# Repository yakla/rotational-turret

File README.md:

# infinit Rotational Smart Tracking Camera

first i started the project as a idea for a consept for a rotating turret that can go forever without needing to retract. i wanted to make it a concept so i made the build realy small but after i designed the base and then decited to go all out and make a follower cammera. in the end it ended up super small in just 10cm×10cm×9cm. for me its just a fun project to do in the meantime of the war currently. 

## Mechanics & Power
The project uses a high speed brushless motor to rotate the base gear and a very small servo to rotate the head.
The power uses usb c 12v and buck convertor to power everything and passes the data and the power throught a slip ring  inside the shaft .

## Communication & Vision Pipeline
To comunicate with other devices and transfer the stream it uses a udp server to get the ip of the device and send back the camera data to it for high speed transfer and low cpu usage on the small esp . 
It also uses bluetooth for manual movment mode. 
For the color pipeline i use a optimised version of rgb to hsv and color range checking for each pixel summing the position and getting the aproximet position to rotate to.

## Modes
the turret has 3 main modes.
* Manual that streams with jpeg optimised stream and let the user control the turret
* Follower that sets the turret to follow the target (for now set in the code)
* Lock that send the data of the target position without following it

## Design & Hardware
For the head i designed a costume pcb to fit the tof sensor the esp camera and the leds.
For a encloseure i use a thin sheet of invisable plastic that rotates with the turret. that make it realy cool in my opinion.

CAD Link : https://cad.onshape.com/documents/5493d3bfb7c584824d124c44/w/b9fe300d7cd71857bff2772f/e/d3c804d532ca15a2a7af37b9?renderMode=0&uiState=69b6b6c78c596208d828381b

For the Hardware i used:
* XIAO ESP32-S3 - Main Controller & Vision Processing
* PTK 7308H Servo - Pan/Tilt Movement
* Emax ECO 1407 Motor - Turret Movement
* Custom PCB - Power distribution, Leds & sensor integration
*  - Distance detection (ToF)
   - Camera OV2640
   - SK6805 NeoPixel

## Project Status & Roadmap
- [ ] Mobile App for Remote control and setting Wifi detection and simple viewing window (Planned)
- [x] Design the project with a cheaper servo (Planned) 

## How to use
* **Build:** Use PlatformIO to flash the Firmware/ folder to the XIAO.
* **Setup_bluetooth:** Connect to the device via Bluetooth.
* **Setup_wifi:** Currently have to set it in the main code. will probebly add a way in the app later
* **UDP_client** you can use the python code in tools folder of the firmware currently. Will add a viewing window in the app later
* **Run:** Point the camera at a target object; the turret will lock on using the HSV threshold defined in config.h.

## Credits
* Designed and built as part of Hack Club.

## BOM
| Item                               | Description                                                   | Quantity             | Unit Price ($) | Total Price ($) | URL |
|:-----------------------------------|:--------------------------------------------------------------|:---------------------|:---------------|:----------------|:----|
| Hobbywing Skywalker 12A            | esc for the brushless motor                                   | 1                    | $5.23          | $5.23           | https://he.aliexpress.com/item/1005006848267224.html |
| Emax ECO 1407 Motor 2800KV         | the brushless motor for the base turret rotation              | 1                    | $12.39         | $16.11          | https://he.aliexpress.com/item/1005006857011061.html |
| Ptk 7308h                          | the servo that moves the head of the camera                   | 1                    | $27.00         | $27.16          | https://he.aliexpress.com/item/1005005891940798.html |
| slip ring 6.5mm 8ch a1             | the most important part to move electucity even when rotating | 1                    | $4.04          | $7.04           | https://he.aliexpress.com/item/1005009463382321.html |
| USB-C PD PD/QC Decoy Board         | the usb port                                                  | 1                    | $1.30          | $1.30           | https://he.aliexpress.com/item/1005005622939899.html |
| Mini360 buck convertor             | get the usb voltage down                                      | 1                    | $0.28          | $1.74           |https://he.aliexpress.com/item/1005008724925620.html |
| XIAO ESP32-S3 Sense                | the brain                                                     | 1                    | $13.85         | $17.21          | https://he.aliexpress.com/item/1005005544155799.html |
| Adafruit VL53L4CX                  | the tof sensor                                                | 1                    | $19.57         | $19.57          | https://he.aliexpress.com/item/1005010327402661.html |
| SK6805 2427                        | neopixel for the pcb                                          | 1 (50 in one order)  | $3.73          | $6.30           | https://he.aliexpress.com/item/1005008979678361.html|
| capcacitor 100nf 0805              | just there for the neopixel                                   | 1 (100 in one order) | $1.24          | $1.24           | https://he.aliexpress.com/item/1005005293453925.html |
| capcacitor 10uf 1206               | just there for the neopixel                                   | 1 (20 in one order)  | $1.35          | $1.35           | https://he.aliexpress.com/item/1005007363840397.html |
| resestor 47R 0805                  | for the neopixel din                                          | 1 (100 in one order) | $1.11          | $1.11           | https://he.aliexpress.com/item/32382494431.html |
|o-ring thickring 2mm 26mm od        |for the conveyor of the head spin                              |1(100 in one order)   |1.99$           |$1.99            |https://he.aliexpress.com/item/1005006851111300.html |
|PCB                              	 |the PCB	             |1 (5 for one order)	                 |$2.00	                |$7.29|https://www.elecrow.com
|6000-2RS Bearing 10mm id 26mm od|for low friction shaft rotation|1 (4 for one order)|$3.12|$3.12|https://he.aliexpress.com/item/1005006079201259.html|
|Clamp shaft lock Ring Collar 10mm|to hold the shaft better|1|$2.73|$2.73|https://he.aliexpress.com/item/1005006211797860.html|
**Sum** |                                                               |                      | **$100.93** | **$120.49** current price **$105.10** | |

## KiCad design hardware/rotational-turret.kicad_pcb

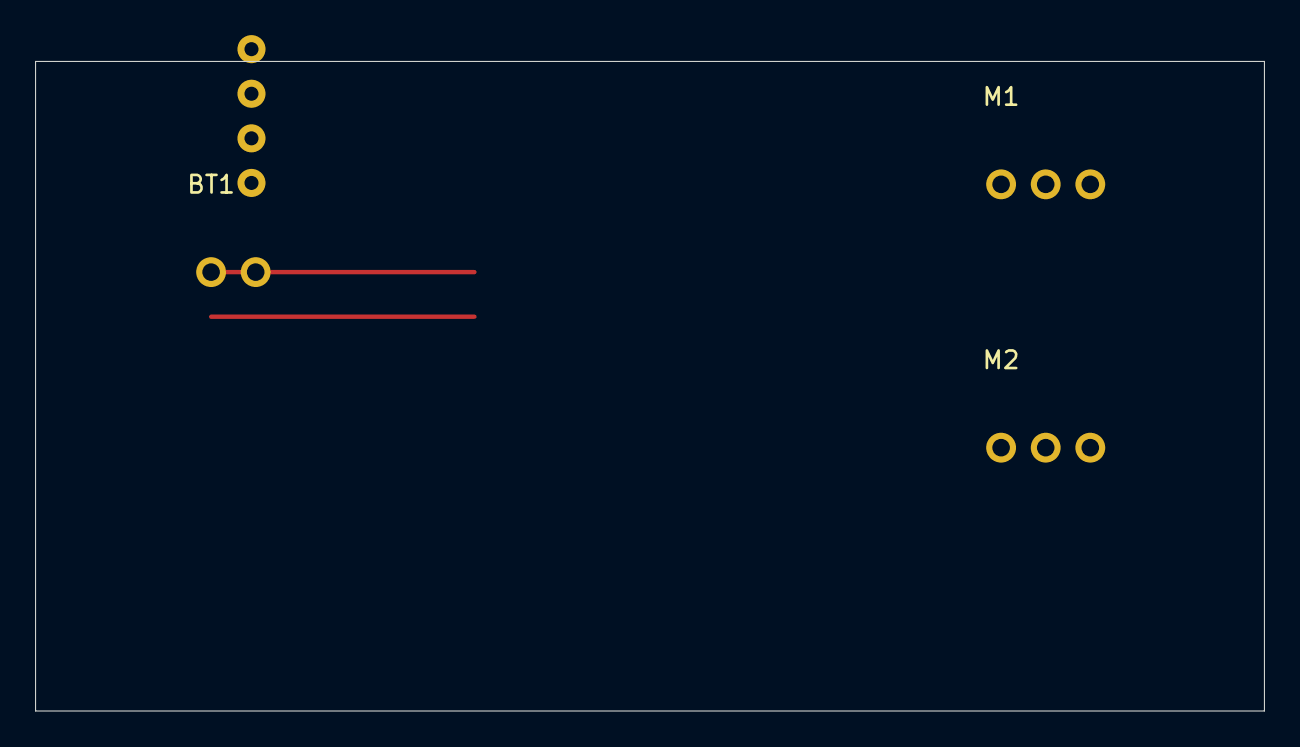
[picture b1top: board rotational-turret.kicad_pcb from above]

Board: 2 copper layers, 70.0 x 37.0 mm, 4 parts (0 on the bottom side), 4 nets.

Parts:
BT1: 7.4V_LiPo; PinHeader_1x02_P2.54mm_Vertical
M1: Servo_Pan; PinHeader_1x03_P2.54mm_Vertical
M2: Servo_Tilt; PinHeader_1x03_P2.54mm_Vertical
U1: NodeMCU-v1.0

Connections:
D1: M1.3, U1.3
D2: M2.3, U1.4
GND: BT1.2, M1.1, M2.1, U1.2
VCC: BT1.1, M1.2, M2.2, U1.1

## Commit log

2026-03-08 Initial plan
2026-03-08 Add ESP8266 firmware and KiCad PCB design for rotational turret
2026-03-09 Initial PCB design for turret project
2026-03-09 Change directory config
2026-03-09 Update README with project screenshot and description
    Added a screenshot and project description to README.
2026-03-09 update the pcb a bit
2026-03-09 add forth pin because i forgot the servo one
2026-03-09 spotless
2026-03-12 update scematic
2026-03-12 update the design slightly
2026-03-12 more things
2026-03-15 Initial clean commit
2026-03-15 add the constants Hsv filter
2026-03-15 Add footprints and schematics to the project folder
2026-03-15 Clean up README.md and remove duplicate CAD link
    Removed duplicate CAD link section and fixed minor typos.
2026-03-15 Fix typos and enhance README content
    Corrected typos and improved clarity in the README.
2026-03-16 more updates
2026-03-16 Configure Secret Detection in `.gitlab-ci.yml`, creating this file if it does not already exist
2026-03-16 commit alll
2026-03-16 Edit README.md
2026-03-17 another one commit
